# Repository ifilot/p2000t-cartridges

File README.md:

# P2000T Cartridges

## Purpose
Set of homebrew multirom cartridges for the P2000T. These cartridges contain
multiple ROM files stored on a single parallel EEPROM chip. The user can select
the desired program using a DIP switch. More information on these cartridges can
be found [on the website](https://www.philips-p2000t.nl/).

> [!TIP] 
> Have questions or comments about the **P2000T Cartridges**? Join
> the conversation and chat with the developers on our [Discord
> server](https://discord.gg/YtzJTWYAxy).

## MultiROM cartridges

> [!TIP]
> * Unsure which cartridge is right for you? The 32x16KiB THT SST39SF040 
>   (512 KiB ROM) offers the most features and is relatively straightforward to 
>   assemble with soldering.
> * When ordering the cartridges, it is advisable to choose an ENIG finish, 
>   opt for gold fingers, and specify a 30-degree chamfer on the edge connector.
> * For flashing the SST39SF0x0 chips, there is [a cheap Flasher tool](https://github.com/ifilot/pico-sst39sf0x0-programmer)
    available, based on the Raspberry Pi PICO.
> * A premade set of cartridge ROM-packs can be found [here](https://github.com/ifilot/p2000t-rompacks).

### 32x16KiB THT SST39SF040 (512 KiB ROM)

A SLOT1 cartridge designed to enable selection from 32 memory banks, assuming
the use of a 512KB ROM chip. It features a dedicated bracket PCB for holding the
DIP switch, which can be connected to the main PCB using either six wires or a
custom flex cable. Additionally, this cartridge includes a soft reset switch,
equipped with a debouncing circuit using a 74HC123 multivibrator. This cartridge
uses **THT** components.

* [PCB - Multicartridge](multicartridge-tht-top-dipswitch/pcb)
* [PCB - DIP switch plate](multicartridge-tht-top-dipswitch/pcb/dipswitch-plate)
* [Flexcable](multicartridge-tht-top-dipswitch/pcb/flexconnector)
* [Casing (3d-print files)](multicartridge/case)

### 32x16KiB SMD SST39SF040 (512 KiB ROM)

Similar to the 32x16KiB THT SST39SF040 cartridge, this version utilizes **SMD**
components, with the exception of the PLCC32 THT socket used for the SST39SF040
chip. Design schematics for the DIP switch plate and the flexcable can be found
under the `THT` variant. Position and BOM files are provided for assembly
service.

* [PCB - Multicartridge](multicartridge-smd-top-dipswitch/pcb)
* [PCB - DIP switch plate](multicartridge-tht-top-dipswitch/pcb/dipswitch-plate)
* [Flexcable](multicartridge-tht-top-dipswitch/pcb/flexconnector)
* [Casing (3d-print files)](multicartridge/case)

### 4 x 16KiB THT W27C512 (64 KiB ROM)

There is also a MultiROM cartridge featuring the reliable W27C512 chip, offering
4x16KB of storage. Unlike the 512KB version, this cartridge omits the soft reset
functionality as a cost-saving measure.

* [PCB - Multicartridge](multicartridge-w27c512/pcb)
* [Casing (3d-print files)](multicartridge-w27c512/case)

### Multirom cartridge - ZIF

SLOT1 cartridge that allows the user to select one of 32 banks (assuming a 512kb
ROM chip is used). Instead of a fixed ROM chip, this cartridge uses a ZIF socket
for easy exchange of the ROM chip. The cartridge also contains a soft reset
switch.

* [PCB](multicartridge-zif/pcb/p2000t-multicartridge-zif)
* [Casing (3d-print files)](multicartridge-zif/case)

### MultiROM cartridge kit (smd)

Simplified version of the SST39SF040 / 512kb cartridge meant for easy soldering.
This cartridge assumes that the SMD components are already placed using an
assembly service of the PCB manufacturer.

* [PCB](multicartridge-smd/pcb)
* [Casing (3d-print files)](multicartridge-smd/case)

## Enclosures

All enclosures have so-called mouse ears which helps in the adhesion
of the enclosure to the print plate. This prevents warping.

Recommended print settings for the enclosures:
* 0.4mm nozzle
* 0.20 - 0.25mm layer height
* 10%-20% infill

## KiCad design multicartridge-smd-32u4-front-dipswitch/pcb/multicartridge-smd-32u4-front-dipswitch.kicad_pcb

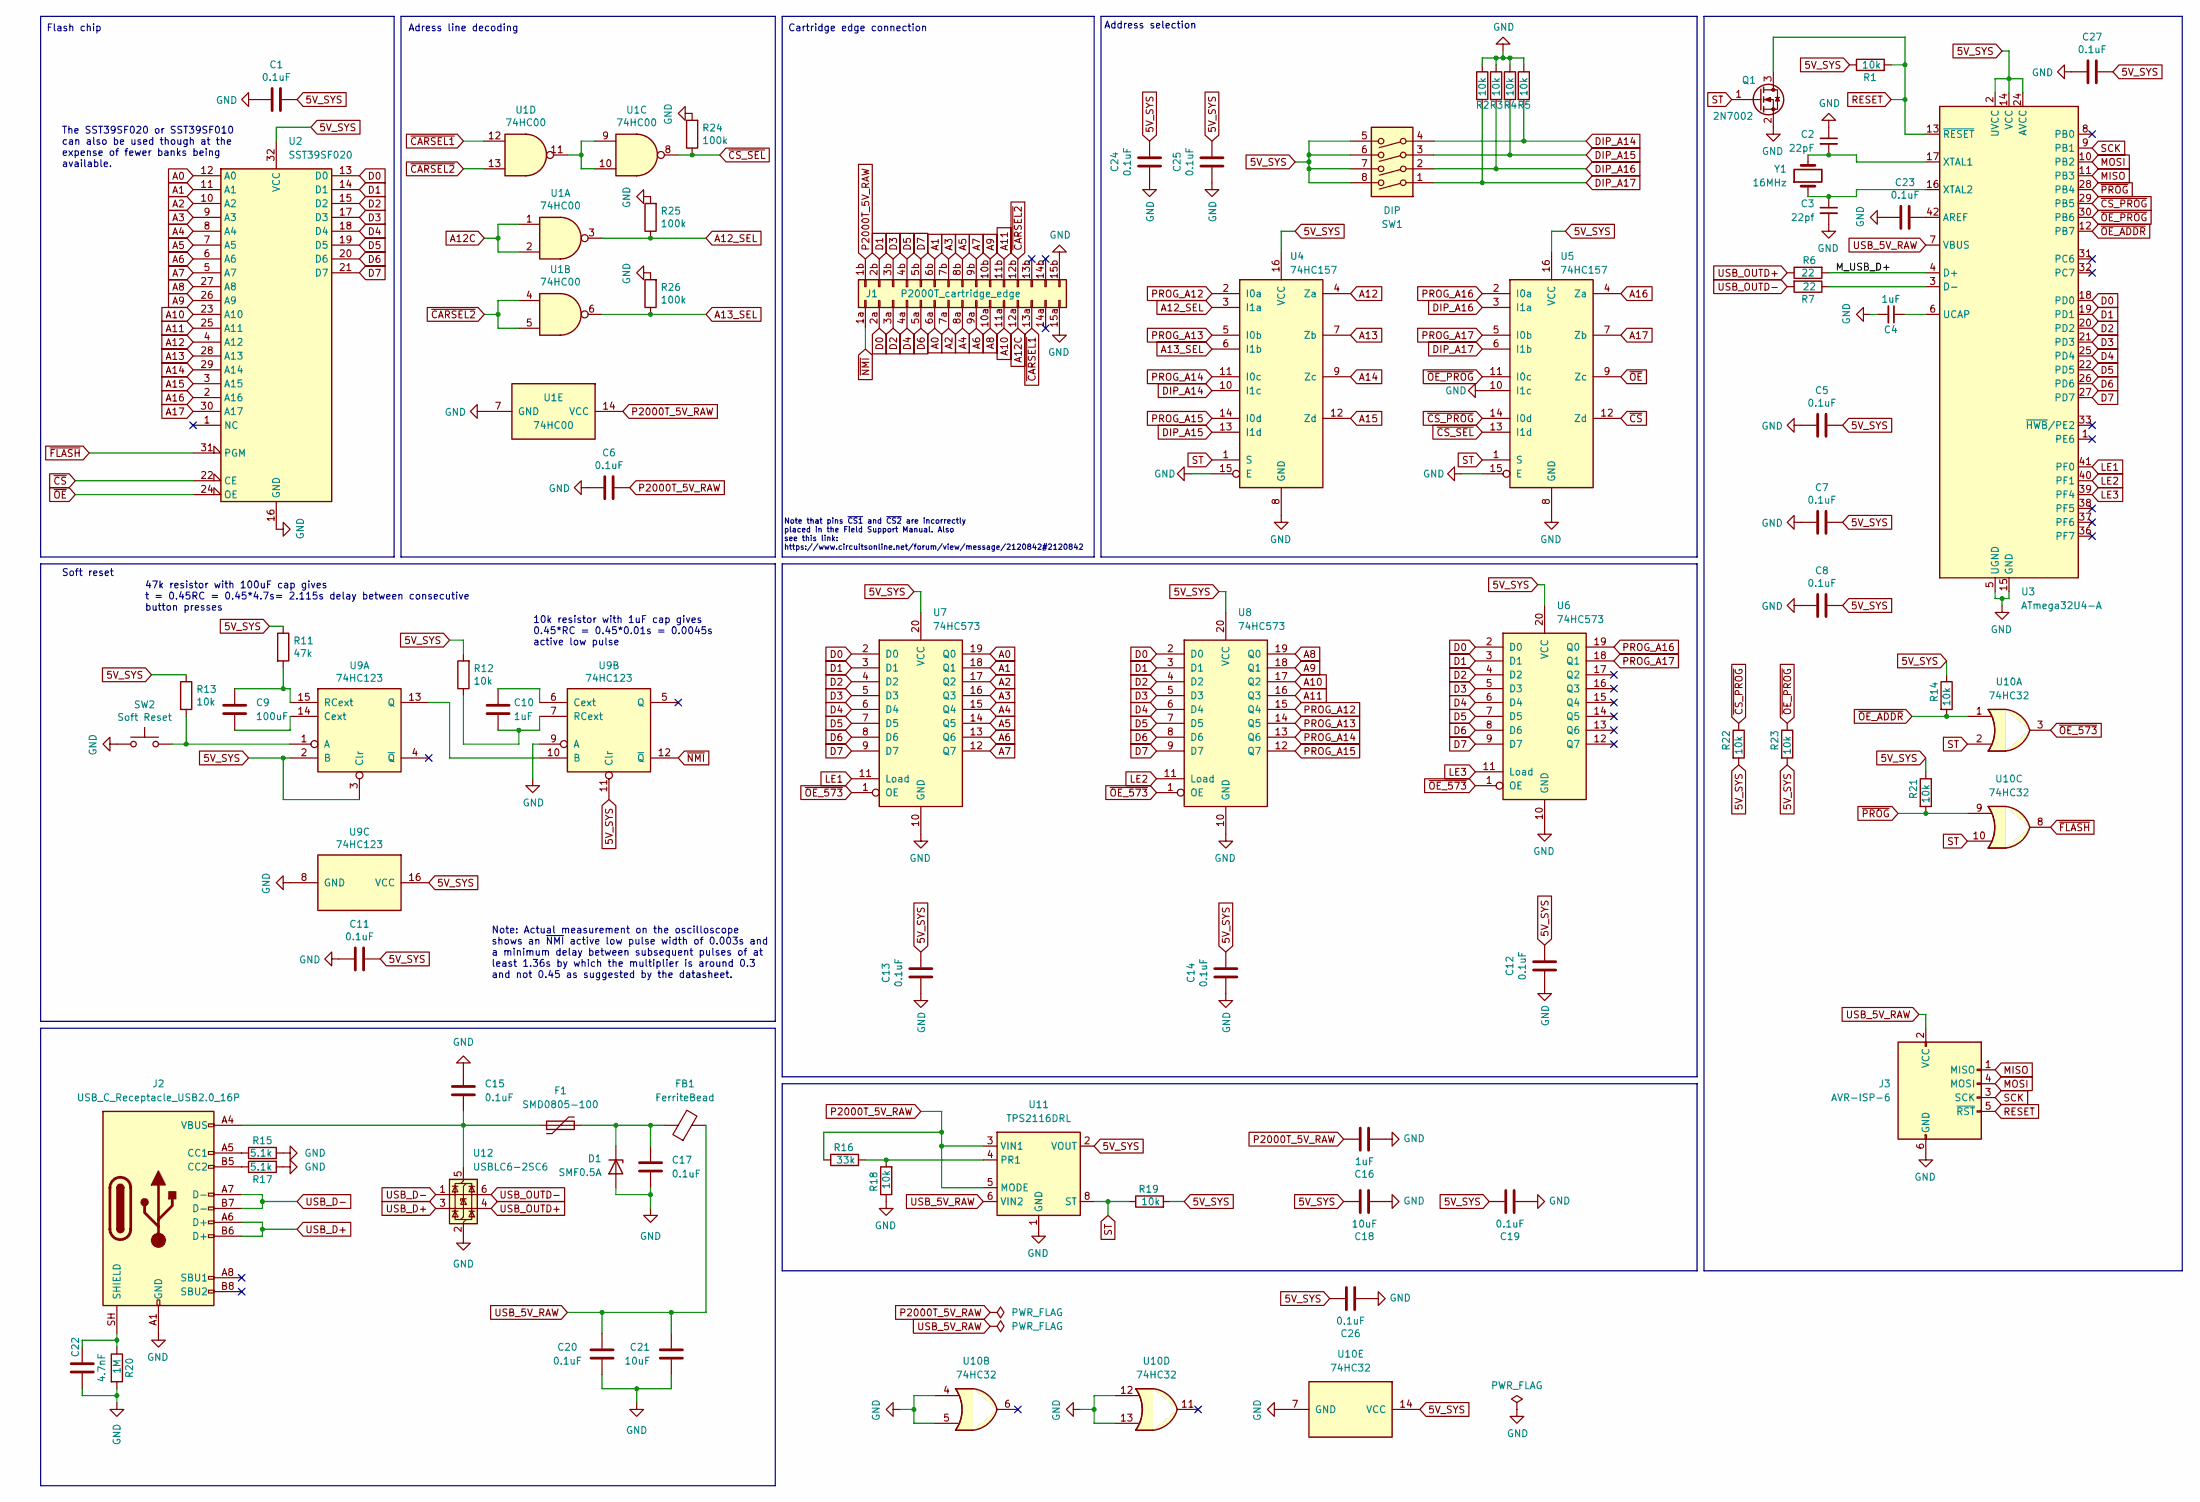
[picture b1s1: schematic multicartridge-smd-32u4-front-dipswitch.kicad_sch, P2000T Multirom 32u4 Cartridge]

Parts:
C1, C5, C6, C7, C8, C11, C12, C13, C14, C15, C17, C19, C20, C23, C24, C25, C26, C27: 0.1uF; C_0805_2012Metric; LCSC C28233
C2: 22pF; C_0805_2012Metric; LCSC C1804
C3: 22pf; C_0805_2012Metric; LCSC C1804
C4, C10, C16: 1uF; C_0805_2012Metric; LCSC C28323
C9: 100uF; C_1206_3216Metric; LCSC C15008
C18, C21: 10uF; C_0805_2012Metric; LCSC C15850
C22: 4.7nF; C_0805_2012Metric; LCSC C1744
D1: SMF0.5A; D_SOD-123F; LCSC C20883113
F1: SMD0805-100; Fuse_0805_2012Metric; LCSC C22435710
FB1: FerriteBead; R_0805_2012Metric; LCSC C1015
J1: P2000T_cartridge_edge; p2000t_cartridge_edge
J2: USB_C_Receptacle_USB2.0_16P; USB_C_Receptacle_HRO_TYPE-C-31-M-12
J3: AVR-ISP-6; IDC-Header_2x03_P2.54mm_Vertical
Q1: 2N7002; SOT-23; LCSC C8545
R1, R2, R3, R4, R5, R12, R13, R14, R18, R19, R21, R22, R23: 10k; C_0805_2012Metric; LCSC C17414
R6, R7: 22; R_0805_2012Metric; LCSC C17561
R11: 47k; C_0805_2012Metric; LCSC C17713
R15, R17: 5.1k; R_0805_2012Metric; LCSC C27834
R16: 33k; C_0805_2012Metric; LCSC C17633
R20: 1M; R_0805_2012Metric; LCSC C27834
R24, R25, R26: 100k; C_0805_2012Metric; LCSC C17514
SW1: DIP; SW_DIP_SPSTx04_Slide_9.78x12.34mm_W7.62mm_P2.54mm
SW2: Soft Reset; SW_PUSH_6mm
U1: 74HC00; SOIC-14_3.9x8.7mm_P1.27mm; LCSC C5586
U2: SST39SF020; PLCC-32_THT-Socket
U3: ATmega32U4-A; TQFP-44_10x10mm_P0.8mm; LCSC C44854
U4, U5: 74HC157; SOIC-16_3.9x9.9mm_P1.27mm; LCSC C5609
U6, U7, U8: 74HC573; SOIC-20W_7.5x12.8mm_P1.27mm; LCSC C5608
U9: 74HC123; SOIC-16_3.9x9.9mm_P1.27mm; LCSC C5597
U10: 74HC32; SOIC-14_3.9x8.7mm_P1.27mm; LCSC C5632
U11: TPS2116DRL; SOT-583-8; LCSC C3235557
U12: USBLC6-2SC6; SOT-23-6; LCSC C2687116
Y1: 16MHz; Crystal_HC49-U_Vertical

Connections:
5V_SYS: C1.1, C5.1, C7.1, C8.1, C11.1, C12.1, C13.1, C14.1, C18.1, C19.1, C24.1, C25.1, C26.1, C27.1, R1.1, R11.1, R12.2, R13.1, R14.1, R19.2, R21.1, R22.2, R23.2, SW1.5, SW1.6, SW1.7, SW1.8, U2.32 (VCC), U3.2 (UVCC), U3.14 (VCC), U3.24 (AVCC), U3.34 (VCC), U3.44 (AVCC), U4.16 (VCC), U5.16 (VCC), U6.20 (VCC), U7.20 (VCC), U8.20 (VCC), U9.2 (B), U9.3 (Clr), U9.11 (Clr), U9.16 (VCC), U10.14 (VCC), U11.2 (VOUT), U11.7 (VOUT)
/M_USB_D+: R6.2, U3.4 (D+)
A0: J1.6a, U2.12 (A0), U7.19 (Q0)
A1: J1.6b, U2.11 (A1), U7.18 (Q1)
A2: J1.7a, U2.10 (A2), U7.17 (Q2)
A3: J1.7b, U2.9 (A3), U7.16 (Q3)
A4: J1.8a, U2.8 (A4), U7.15 (Q4)
A5: J1.8b, U2.7 (A5), U7.14 (Q5)
A6: J1.9a, U2.6 (A6), U7.13 (Q6)
A7: J1.9b, U2.5 (A7), U7.12 (Q7)
A8: J1.10a, U2.27 (A8), U8.19 (Q0)
A9: J1.10b, U2.26 (A9), U8.18 (Q1)
A10: J1.11a, U2.23 (A10), U8.17 (Q2)
A11: J1.11b, U2.25 (A11), U8.16 (Q3)
A12: U2.4 (A12), U4.4 (Za)
A12C: J1.12a, U1.1, U1.2
A12_SEL: R25.1, U1.3, U4.3 (I1a)
A13: U2.28 (A13), U4.7 (Zb)
A13_SEL: R26.1, U1.6, U4.6 (I1b)
A14: U2.29 (A14), U4.9 (Zc)
A15: U2.3 (A15), U4.12 (Zd)
A16: U2.2 (A16), U5.4 (Za)
A17: U2.30 (A17), U5.7 (Zb)
D0: J1.2a, U2.13 (D0), U3.18 (PD0), U6.2 (D0), U7.2 (D0), U8.2 (D0)
D1: J1.2b, U2.14 (D1), U3.19 (PD1), U6.3 (D1), U7.3 (D1), U8.3 (D1)
D2: J1.3a, U2.15 (D2), U3.20 (PD2), U6.4 (D2), U7.4 (D2), U8.4 (D2)
D3: J1.3b, U2.17 (D3), U3.21 (PD3), U6.5 (D3), U7.5 (D3), U8.5 (D3)
D4: J1.4a, U2.18 (D4), U3.25 (PD4), U6.6 (D4), U7.6 (D4), U8.6 (D4)
D5: J1.4b, U2.19 (D5), U3.22 (PD5), U6.7 (D5), U7.7 (D5), U8.7 (D5)
D6: J1.5a, U2.20 (D6), U3.26 (PD6), U6.8 (D6), U7.8 (D6), U8.8 (D6)
D7: J1.5b, U2.21 (D7), U3.27 (PD7), U6.9 (D7), U7.9 (D7), U8.9 (D7)
DIP_A14: R5.2, SW1.4, U4.10 (I1c)
DIP_A15: R4.2, SW1.3, U4.13 (I1d)
DIP_A16: R3.2, SW1.2, U5.3 (I1a)
DIP_A17: R2.2, SW1.1, U5.6 (I1b)
GND: C1.2, C2.1, C3.2, C4.2, C5.2, C6.2, C7.2, C8.2, C11.2, C12.2, C13.2, C14.2, C15.1, C16.2, C17.2, C18.2, C19.2, C20.2, C21.1, C22.2, C23.2, C24.2, C25.2, C26.2, C27.2, D1.2 (A), J1.15a, J1.15b, J2.A1 (GND), J2.A12 (GND), J2.B1 (GND), J2.B12 (GND), J3.6 (GND), Q1.2 (S), R2.1, R3.1, R4.1, R5.1, R15.2, R17.2, R18.1, R20.2, R24.2, R25.2, R26.2, SW2.1, U1.7 (GND), U2.16 (GND), U3.5 (UGND), U3.15 (GND), U3.23 (GND), U3.35 (GND), U3.43 (GND), U4.8 (GND), U4.15 (E), U5.8 (GND), U5.10 (I1c), U5.15 (E), U6.10 (GND), U7.10 (GND), U8.10 (GND), U9.8 (GND), U9.9 (A), U10.4, U10.5, U10.7 (GND), U10.12, U10.13, U11.1 (GND), U12.2 (GND)
LE1: U3.41 (PF0), U7.11 (Load)
LE2: U3.40 (PF1), U8.11 (Load)
LE3: U3.39 (PF4), U6.11 (Load)
MISO: J3.1 (MISO), U3.11 (PB3)
MOSI: J3.4 (MOSI), U3.10 (PB2)
unnamed: C17.1, D1.1 (K), F1.2, FB1.1
unnamed: J2.A5 (CC1), R15.1
unnamed: J2.B5 (CC2), R17.1
unnamed: C22.1, J2.SH (SHIELD), R20.1
unnamed: U1.9, U1.10, U1.11
unnamed: C23.1, U3.42 (AREF)
unnamed: R7.1, U3.3 (D-)
unnamed: C4.1, U3.6 (UCAP)
unnamed: C2.2, U3.17 (XTAL1), Y1.2
unnamed: C3.1, U3.16 (XTAL2), Y1.1
unnamed: R13.2, SW2.2, U9.1 (A)
unnamed: C9.2, U9.14 (Cext)
unnamed: U9.10 (B), U9.13 (Q)
unnamed: C9.1, R11.2, U9.15 (RCext)
unnamed: C10.1, U9.6 (Cext)
unnamed: C10.2, R12.1, U9.7 (RCext)
unnamed: R16.2, R18.2, U11.4 (PR1)
unnamed: C15.2, F1.1, J2.A4 (VBUS), J2.A9 (VBUS), J2.B4 (VBUS), J2.B9 (VBUS), U12.5 (VBUS)
P2000T_5V_RAW: C6.1, C16.1, J1.1b, R16.1, U1.14 (VCC), U11.3 (VIN1), U11.5 (MODE)
PROG_A12: U4.2 (I0a), U8.15 (Q4)
PROG_A13: U4.5 (I0b), U8.14 (Q5)
PROG_A14: U4.11 (I0c), U8.13 (Q6)
PROG_A15: U4.14 (I0d), U8.12 (Q7)
PROG_A16: U5.2 (I0a), U6.19 (Q0)
PROG_A17: U5.5 (I0b), U6.18 (Q1)
RESET: J3.5 (~RST), Q1.3 (D), R1.2, U3.13 (~RESET)
SCK: J3.3 (SCK), U3.9 (PB1)
ST: Q1.1 (G), R19.1, U4.1 (S), U5.1 (S), U10.2, U10.10, U11.8 (ST)
USB_5V_RAW: C20.1, C21.2, FB1.2, J3.2 (VCC), U3.7 (VBUS), U11.6 (VIN2)
USB_D+: J2.A6 (D+), J2.B6 (D+), U12.3 (I/O2)
USB_D-: J2.A7 (D-), J2.B7 (D-), U12.1 (I/O1)
USB_OUTD+: R6.1, U12.4 (I/O2)
USB_OUTD-: R7.2, U12.6 (I/O1)
~CARSEL1: J1.13a, U1.12
~CARSEL2: J1.12b, U1.4, U1.5, U1.13
~CS_PROG: R22.1, U3.29 (PB5), U5.14 (I0d)
~CS_SEL: R24.1, U1.8, U5.13 (I1d)
~CS: U2.22 (CE), U5.12 (Zd)
~FLASH: U2.31 (PGM), U10.8
~NMI: J1.1a, U9.12 (~Q)
~OE_573: U6.1 (OE), U7.1 (OE), U8.1 (OE), U10.3
~OE_ADDR: R14.2, U3.12 (PB7), U10.1
~OE_PROG: R23.1, U3.30 (PB6), U5.11 (I0c)
~OE: U2.24 (OE), U5.9 (Zc)
~PROG: R21.2, U3.28 (PB4), U10.9

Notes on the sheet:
Note that pins ~{CS1} and ~{CS2} are incorrectly placed in the Field Support Manual. Also see this link: https://www.circuitsonline.net/forum/view/message/2120842#2120842
Note: Actual measurement on the oscilloscope shows an ~{NMI} active low pulse width of 0.003s and a minimum delay between subsequent pulses of at least 1.36s by which the multiplier is around 0.3 and not 0.45 as suggested by the datasheet.
Cartridge edge connection
Flash chip
Adress line decoding
The SST39SF020 or SST39SF010 can also be used though at the expense of fewer banks being available.
Soft reset
47k resistor with 100uF cap gives t = 0.45RC = 0.45*4.7s= 2.115s delay between consecutive button presses
10k resistor with 1uF cap gives 0.45*RC = 0.45*0.01s = 0.0045s active low pulse
Address selection

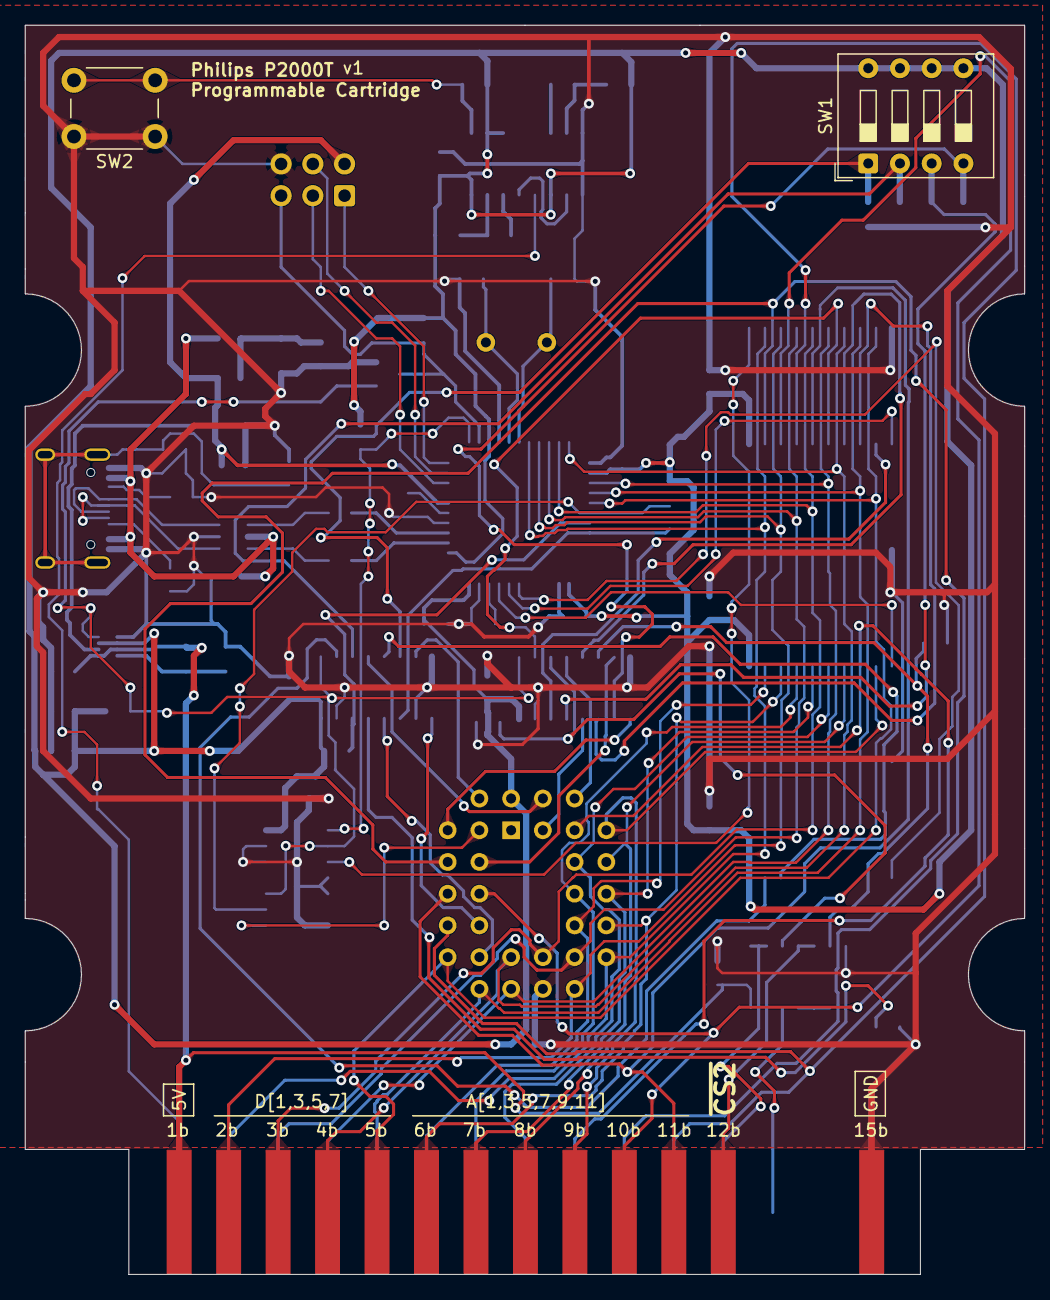
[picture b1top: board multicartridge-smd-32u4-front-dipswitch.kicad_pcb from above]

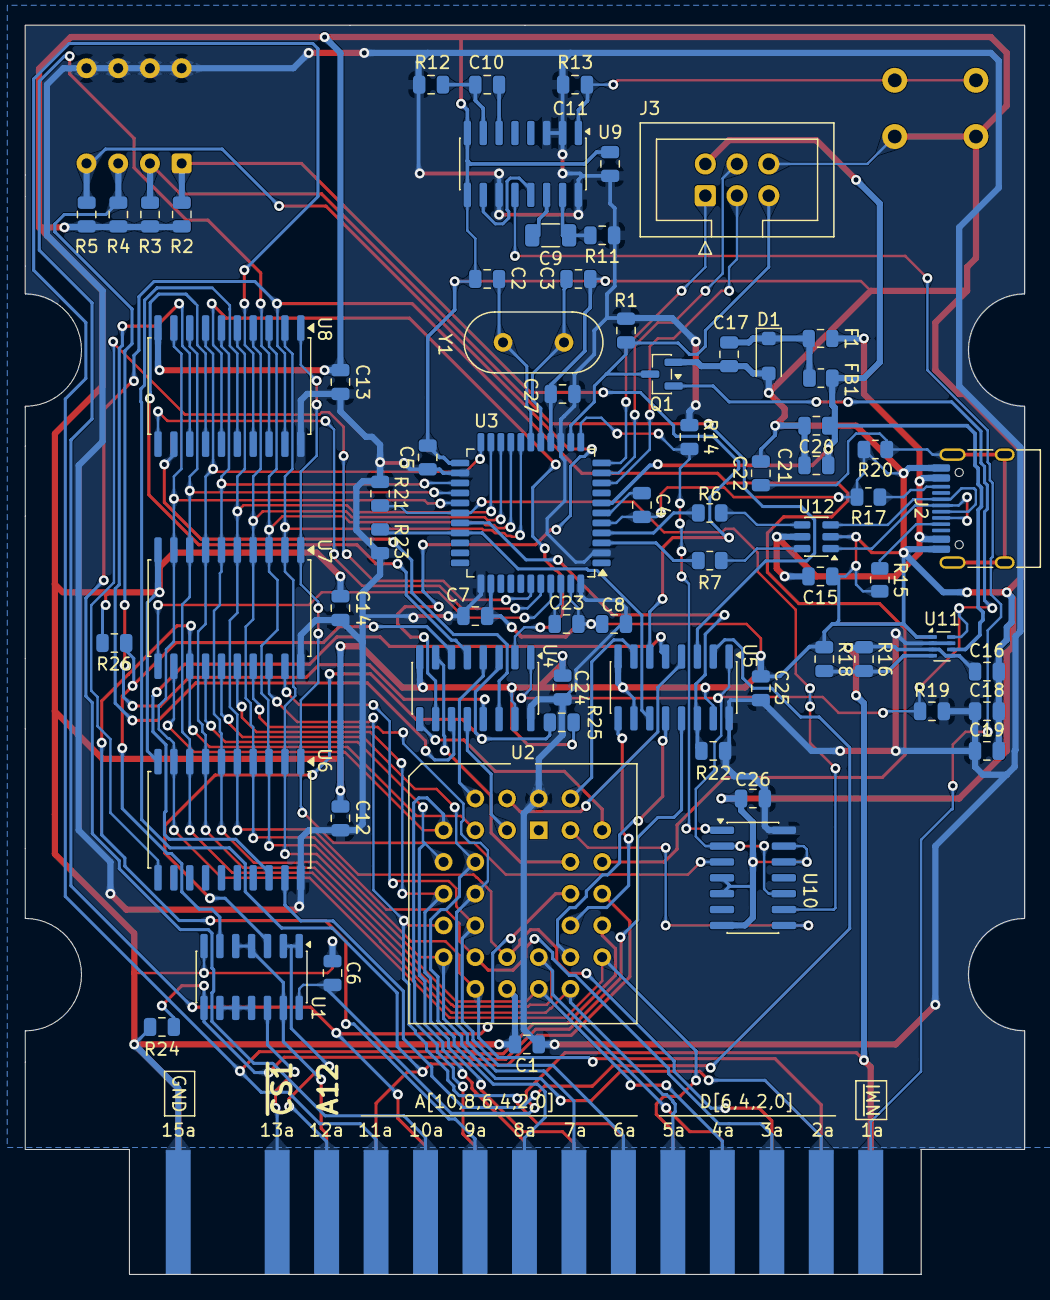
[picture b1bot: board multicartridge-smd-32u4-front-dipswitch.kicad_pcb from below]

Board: 2 copper layers, 80.0 x 100.0 mm, 72 parts (70 on the bottom side), 86 nets.

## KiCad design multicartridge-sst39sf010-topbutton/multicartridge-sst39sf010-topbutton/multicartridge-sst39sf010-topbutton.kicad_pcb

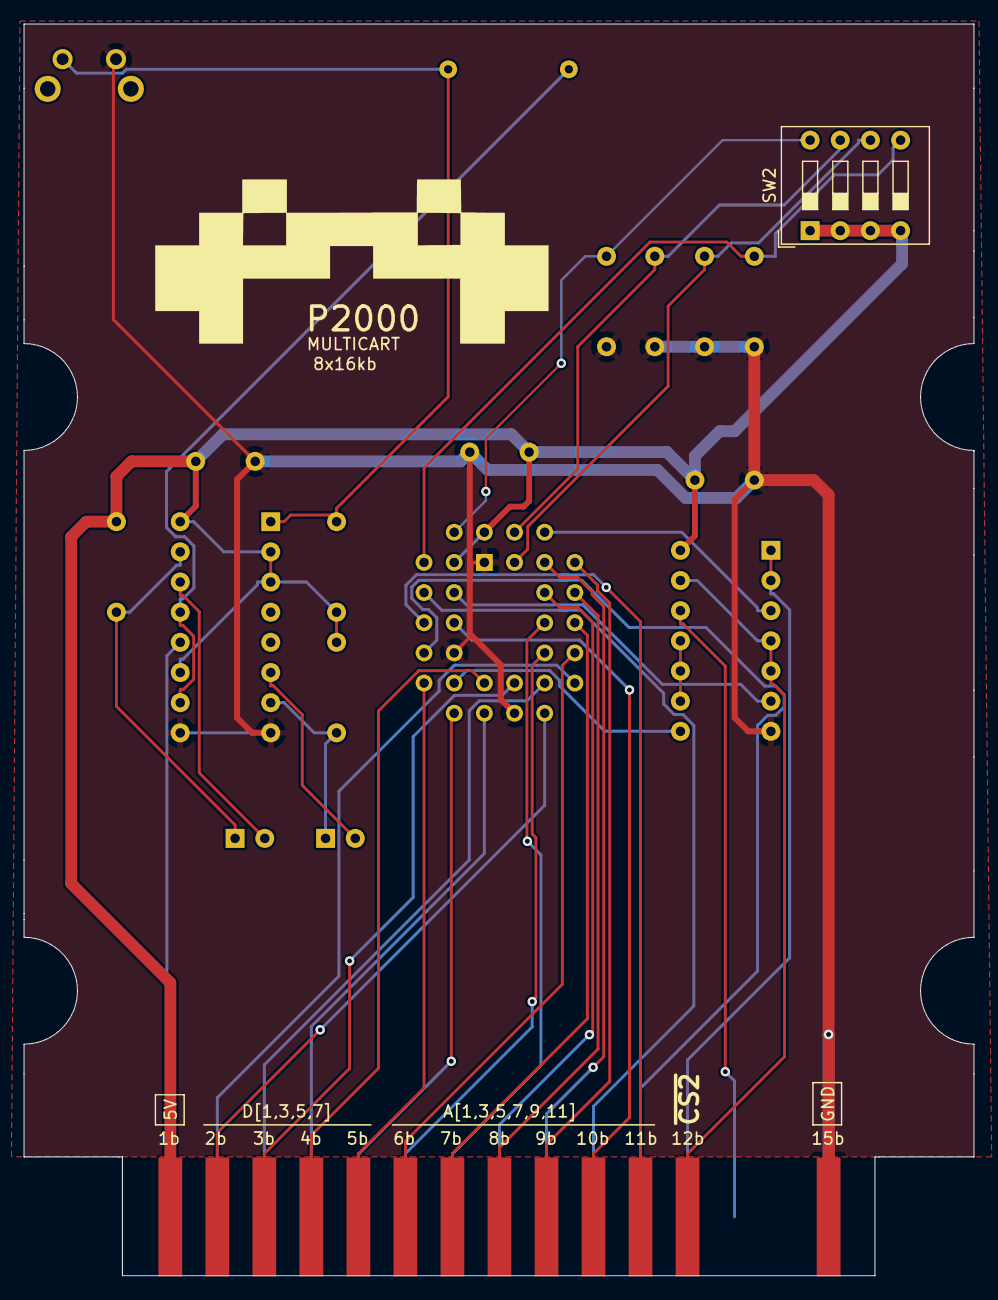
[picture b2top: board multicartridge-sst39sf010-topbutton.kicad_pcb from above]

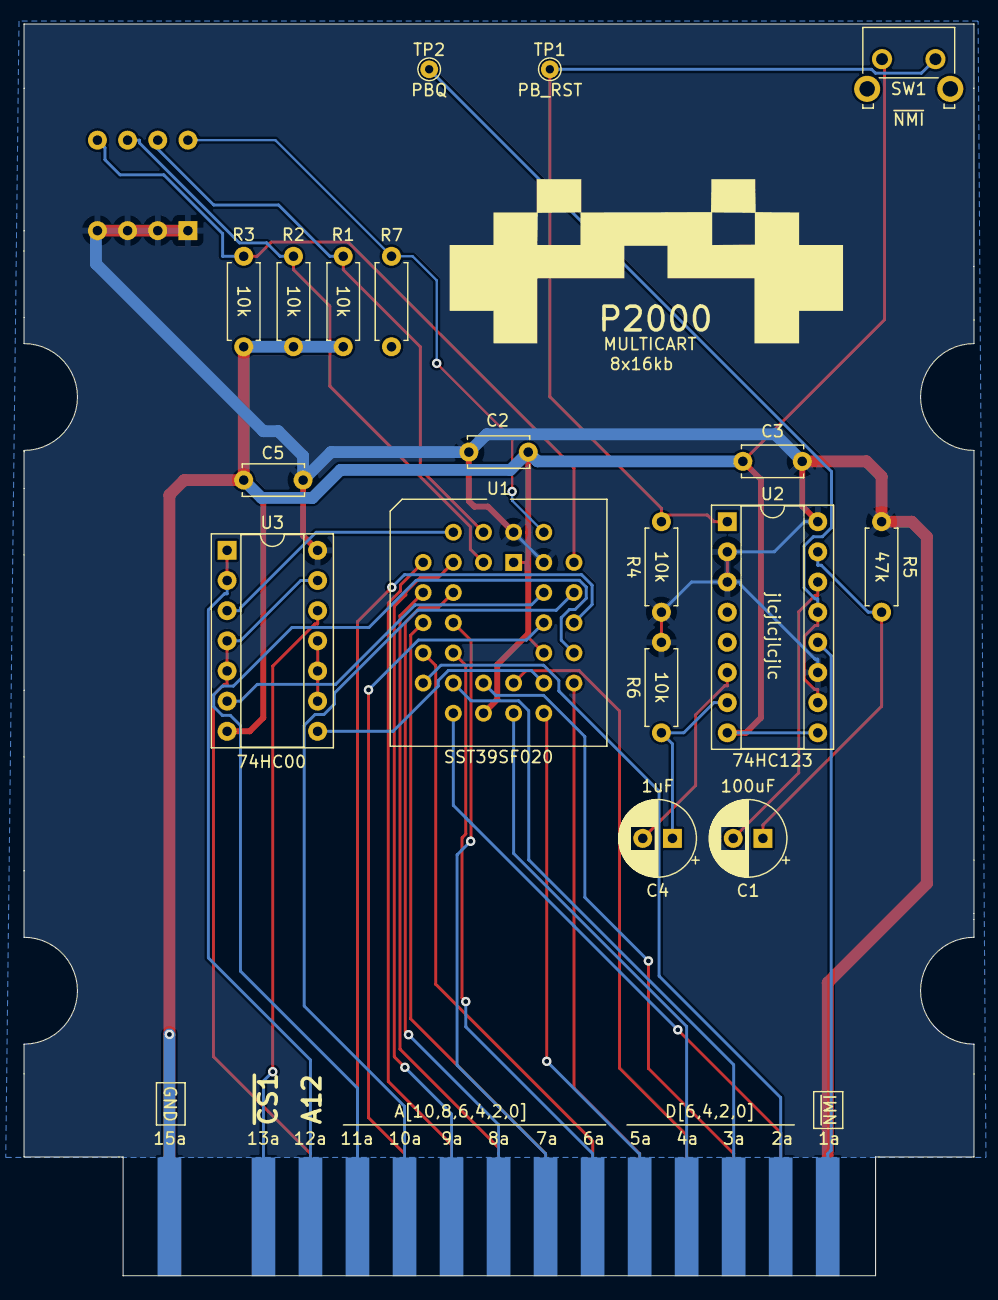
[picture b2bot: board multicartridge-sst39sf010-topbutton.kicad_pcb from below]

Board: 2 copper layers, 80.0 x 105.4 mm, 22 parts (20 on the bottom side), 40 nets.

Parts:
C1: 100uF; CP_Radial_D6.3mm_P2.50mm
C2, C3, C5: 0.1uF; C_Disc_D5.0mm_W2.5mm_P5.00mm
C4: 1uF; CP_Radial_D6.3mm_P2.50mm
G001, G002: LOGO; fraxxon_goblin_shooter
J1: P2000T_cartridge_edge; p2000t_cartridge_edge
R1, R2, R3, R4, R6, R7: 10k; R_Axial_DIN0207_L6.3mm_D2.5mm_P7.62mm_Horizontal
R5: 47k; R_Axial_DIN0207_L6.3mm_D2.5mm_P7.62mm_Horizontal
SW1: ~{NMI}; SW_Tactile_SKHH_Angled
SW2: SW_DIP_x04; SW_DIP_SPSTx04_Slide_9.78x12.34mm_W7.62mm_P2.54mm
TP1: PB_RST; TestPoint_THTPad_D1.5mm_Drill0.7mm
TP2: PBQ; TestPoint_THTPad_D1.5mm_Drill0.7mm
U1: SST39SF020; PLCC-32_THT-Socket
U2: 74HC123; DIP-16_W7.62mm_Socket
U3: 74HC00; DIP-14_W7.62mm_Socket

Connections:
+5V: C2.1, C3.1, C5.1, J1.1b, R4.1, R5.1, R6.2, SW2.1, SW2.2, SW2.3, SW2.4, U1.31 (PGM), U1.32 (VCC), U2.2 (B), U2.3 (Clr), U2.11 (Clr), U2.16 (VCC), U3.14 (VCC)
A0: J1.6a, U1.12 (A0)
A1: J1.6b, U1.11 (A1)
A2: J1.7a, U1.10 (A2)
A3: J1.7b, U1.9 (A3)
A4: J1.8a, U1.8 (A4)
A5: J1.8b, U1.7 (A5)
A6: J1.9a, U1.6 (A6)
A7: J1.9b, U1.5 (A7)
A8: J1.10a, U1.27 (A8)
A9: J1.10b, U1.26 (A9)
A10: J1.11a, U1.23 (A10)
A11: J1.11b, U1.25 (A11)
A12: U1.4 (A12), U3.3
A12C: J1.12a, U3.1, U3.2
A13: U1.28 (A13), U3.6
A14: R3.2, SW2.5, U1.29 (A14)
A15: R2.2, SW2.6, U1.3 (A15)
A16: R1.2, SW2.7, U1.2 (A16)
A17: R7.2, SW2.8, U1.30 (A17)
D0: J1.2a, U1.13 (D0)
D1: J1.2b, U1.14 (D1)
D2: J1.3a, U1.15 (D2)
D3: J1.3b, U1.17 (D3)
D4: J1.4a, U1.18 (D4)
D5: J1.4b, U1.19 (D5)
D6: J1.5a, U1.20 (D6)
D7: J1.5b, U1.21 (D7)
GND: C2.2, C3.2, C5.2, J1.15a, J1.15b, R1.1, R2.1, R3.1, R7.1, SW1.1, U1.1 (NC), U1.16 (GND), U1.24 (OE), U2.8 (GND), U2.9 (A), U3.7 (GND)
unnamed: R4.2, SW1.2, TP1.1, U2.1 (A)
unnamed: C1.2, U2.14 (Cext)
unnamed: TP2.1, U2.10 (B), U2.13 (Q)
unnamed: C1.1, R5.2, U2.15 (RCext)
unnamed: C4.2, U2.6 (Cext)
unnamed: C4.1, R6.1, U2.7 (RCext)
unnamed: U3.9, U3.10, U3.11
~CARSEL1: J1.13a, U3.12
~CARSEL2: J1.12b, U3.4, U3.5, U3.13
~CS: U1.22 (CE), U3.8
~NMI: J1.1a, U2.12 (~Q)

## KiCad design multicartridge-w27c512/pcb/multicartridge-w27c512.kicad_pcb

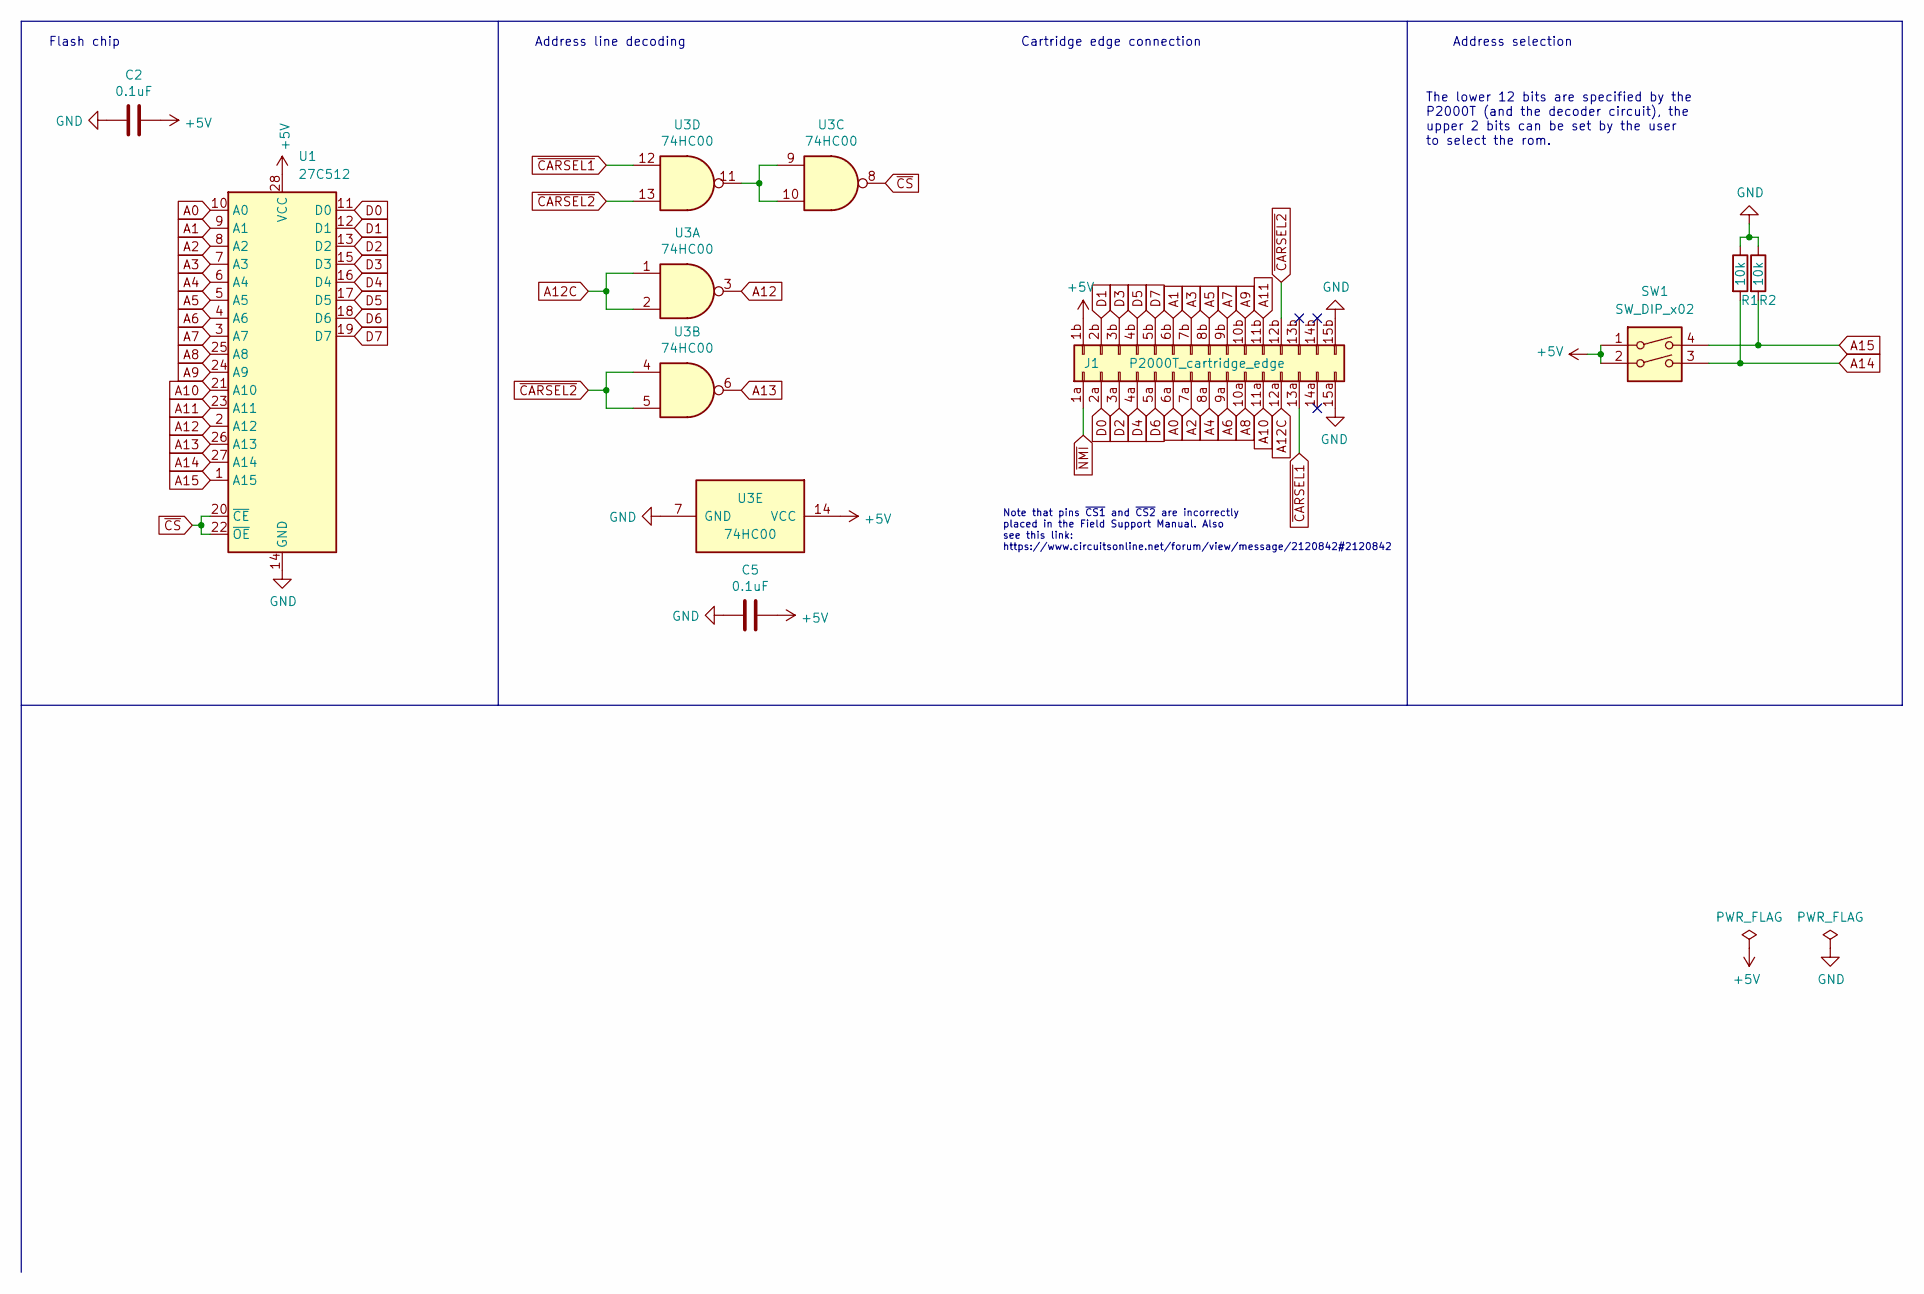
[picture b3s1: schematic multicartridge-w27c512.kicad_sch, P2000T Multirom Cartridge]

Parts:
C2, C5: 0.1uF; C_Disc_D5.0mm_W2.5mm_P5.00mm
J1: P2000T_cartridge_edge; p2000t_cartridge_edge
R1, R2: 10k; R_Axial_DIN0207_L6.3mm_D2.5mm_P7.62mm_Horizontal
SW1: SW_DIP_x02; SW_DIP_SPSTx02_Slide_9.78x7.26mm_W7.62mm_P2.54mm
U1: 27C512; DIP-28_W15.24mm_Socket
U3: 74HC00; DIP-14_W7.62mm_Socket

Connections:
+5V: C2.1, C5.1, J1.1b, SW1.1, SW1.2, U1.28 (VCC), U3.14 (VCC)
A0: J1.6a, U1.10 (A0)
A1: J1.6b, U1.9 (A1)
A2: J1.7a, U1.8 (A2)
A3: J1.7b, U1.7 (A3)
A4: J1.8a, U1.6 (A4)
A5: J1.8b, U1.5 (A5)
A6: J1.9a, U1.4 (A6)
A7: J1.9b, U1.3 (A7)
A8: J1.10a, U1.25 (A8)
A9: J1.10b, U1.24 (A9)
A10: J1.11a, U1.21 (A10)
A11: J1.11b, U1.23 (A11)
A12: U1.2 (A12), U3.3
A12C: J1.12a, U3.1, U3.2
A13: U1.26 (A13), U3.6
A14: R1.2, SW1.3, U1.27 (A14)
A15: R2.2, SW1.4, U1.1 (A15)
D0: J1.2a, U1.11 (D0)
D1: J1.2b, U1.12 (D1)
D2: J1.3a, U1.13 (D2)
D3: J1.3b, U1.15 (D3)
D4: J1.4a, U1.16 (D4)
D5: J1.4b, U1.17 (D5)
D6: J1.5a, U1.18 (D6)
D7: J1.5b, U1.19 (D7)
GND: C2.2, C5.2, J1.15a, J1.15b, R1.1, R2.1, U1.14 (GND), U3.7 (GND)
unnamed: U3.9, U3.10, U3.11
~CARSEL1: J1.13a, U3.12
~CARSEL2: J1.12b, U3.4, U3.5, U3.13
~CS: U1.20 (~CE), U1.22 (~OE), U3.8
~NMI: J1.1a

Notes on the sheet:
Note that pins ~{CS1} and ~{CS2} are incorrectly placed in the Field Support Manual. Also see this link: https://www.circuitsonline.net/forum/view/message/2120842#2120842
Cartridge edge connection
Flash chip
Address line decoding
The lower 12 bits are specified by the P2000T (and the decoder circuit), the upper 2 bits can be set by the user to select the rom.
Address selection

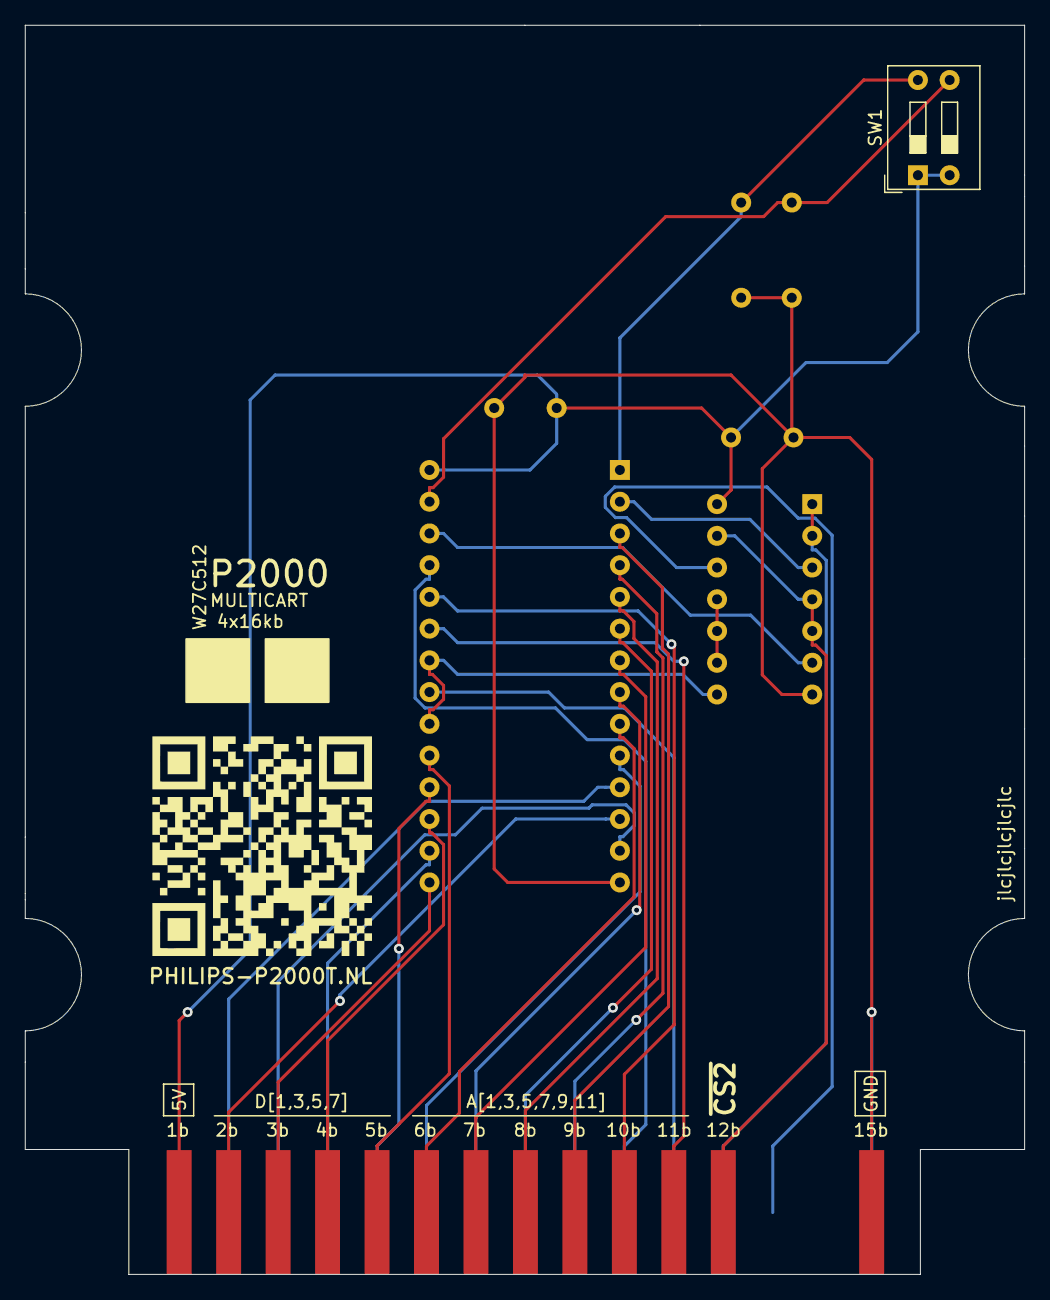
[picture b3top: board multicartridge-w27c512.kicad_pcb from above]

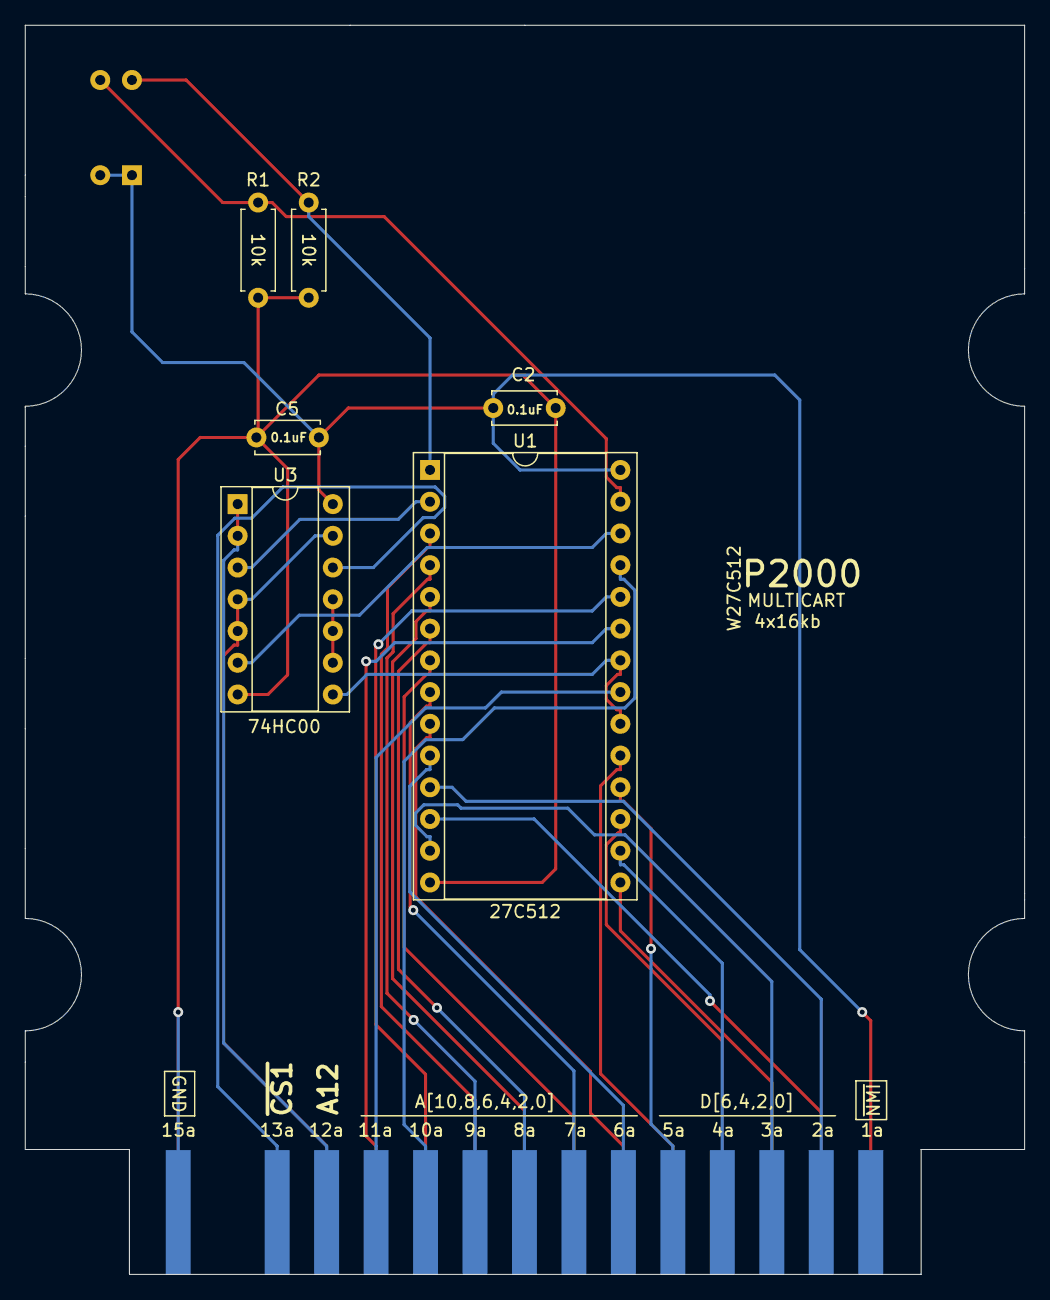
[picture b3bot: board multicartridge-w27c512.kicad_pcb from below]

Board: 2 copper layers, 80.0 x 100.0 mm, 8 parts (7 on the bottom side), 31 nets.

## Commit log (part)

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2023-08-06 Adding cases for multicartridge
2023-08-06 Adding P2000T-multicartridge-plcc32
2023-08-06 Adding ZIF cartridge
2023-08-06 Expanding documentation
2023-08-06 Adding DIP switch plate
2023-08-07 Adding images
2023-09-10 Removing label
2023-09-10 Fixing cases
2023-09-14 Initial commit Multicartridge SMD
2023-09-14 Removing old GERBERS
2023-09-15 Completing PCB
2023-09-15 Updating schematic
2023-09-23 Adding cases
2023-09-23 Updating README.md
2023-09-23 Fixing typo
2023-09-24 Adding labels to cartridges
2024-01-02 Revision of ZIF cartridge
2024-01-12 Adding revised top case
2024-01-13 Revising front case
2024-02-18 Initial commit P2000T cartridge using W27C512 chips
2024-02-27 Tuning access hole
2024-03-01 Updating GERBERS
2024-03-01 Expanding README.md
2024-03-01 Multicartridge w27c512 (#2)
    * Initial commit P2000T cartridge using W27C512 chips
    * Adding cases
    * Tuning access hole
    * Updating GERBERS
    * Expanding README.md
2024-04-03 Tuning lay-out multirom cartridge
2024-04-16 Updating case design
2024-04-26 Adding 4mm inserts for W27C512
2024-04-27 Revising case
2024-06-15 Creating extra cases
2024-07-28 Revising bottom enclosure multirom cartridge
2024-10-12 Improving bottom plate
2024-12-20 Modyfing cases
2025-01-02 Adding STL files and game ROMs
2025-01-02 Adding FLEX PCB
2025-01-06 Adding 8x16kb cartridge for SST39SF010
2025-01-06 Improving case
2025-01-06 Tuning flexcable
2025-01-07 Adding PCB and rewriting README.md
2025-01-07 Fixing links
2025-01-07 Resizing image
2025-01-12 Migrating ROM generation to different repository
2025-01-15 Refining games cartridge
2025-01-25 Updating Case
2025-01-27 Initial commit new design
2025-01-27 Revising design
